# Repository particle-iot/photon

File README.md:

# Photon

The Photon is a tiny WiFi development kit based around USI's WM-N-BM-09 module. This module is a combination of Broadcom's BCM43362 WiFi radio and a STM32F205G microcontroller.

The Photon has a similar footprint and is as close to drop-in compatible as possible with the Spark Core.

### Some highlights of the USI module:

 1. IEEE 802.11b/g/n
 2. Soft AP mode - read smooth WiFi setup process
 3. STM32F205G
 	- 1 MB Flash
 	- 128KB RAM
 	- 120 MHz clock
 4. Measures 12mm x 11mm x 1.3mm

Compared to the Spark Core, the Photon introduces some additional hardware features and changes:

 1. Pin 3V3* is now replaced with VBAT. This pin can be used to power the internal RTC, backup registers and SRAM when the module is put in standby mode.
 2. Pins D1 and D2 can also be used for CAN communication (TX and RX respectively).
 3. Pin A3 now features a DAC (channel 2)
 4. Pin A6 is changed to DAC and exposes a DAC (channel 1).
 5. Pin A7 is changed to WKP (Wakeup). This pin can be used as a standard GPIO, ADC input, PWM or to WAKEUP (rising edge) the module from sleep/standby modes.

A detailed description of the pin mapping can be found in the pin-mapping folder of this repository.
* Sheet 1: Overview of the pin-out.
* Sheet 2: Detailed description of USI module pin-out and its internal mapping to the microcontroller and WiFi radio.

### Pin Descriptions:
- **VIN:** This is the power supply pin to the Photon with a voltage range of 3.6 to 5.5VDC (internally regulated down to 3.3VDC). When the Photon is powered via its USB port, this pin will *ouput* a voltage of approximately 4.7VDC. Why 4.7 and not 5? Well, the actual voltage will be the USB voltage, which is normally 5, minus the forward voltage drop (0.3V) of the protection diode.
- **RST:** This is an active-low reset pin for the Photon.
- **VBAT:** Supply to the internal RTC, backup registers and SRAM (1.8 to 3.3VDC).
- **3V3:** This pin is the output of the on-board regulator and is internally connected to the VDD of the WiFi module. When powering the Photon via VIN or the USB port, this pin will *output* a voltage of 3.3VDC. This pin can also be used to power the Photon directly (max input 3.3VDC). **NOTE:** When powering the Photon via this pin, do not put power on the VIN pin.
- **WKP:** This is an active-high input that allows you to wakeup the module from sleep/deep sleep modes. When not used as a WAKEUP, this pin can also be used as a digital GPIO, ADC input or PWM.
- **D0 - D7:** These are _digital only_ GPIO pins.
- **A0 - A5:** These can be used as digital GPIOs or as ADC inputs.
- **DAC:** This pin can be used as a digital GPIO, ADC input or as a DAC ouput.
- **RX:** Primarily used as UART RX, but can also be used as a digital GPIO, ADC input or PWM.
- **TX:** Primarily used as UART TX, but can also be used as a digital GPIO, ADC input or PWM.

Please review the spreadsheet under the pin-mapping folder to better understand the alternate functions of the GPIO pins.

### Eagle (schematic and pcb layout):
Under the `eagle` folder, you'll find the history of Photon designs.
 1. **cam-drc:** Contains CAM Jobs (for creating gerbers) and DRC (Design Rule) files.
 2. **photon_v001:** The initial photon design.  This version of the design uses the same dimensions as the Spark Core and provides through-hole headers for mounting.
 3. **photon_v010:** Several versions later, numerous tweaks and additions to the schematic, smaller less blinding RGB LED, aligned D7 LED with D7 pin, new SMPS voltage regulator, castellated and non-castellated have been merged, new slightly larger higher gain antenna, Bluetooth Co-existance pins are broken out to pads for a 1.27mm pitch (0.050") connector, pads on the bottom side of the board were added for the RGB LED, and MODE button connections and are centered on the 0.1" grid, and RF switch for software selection of u.FL vs Chip Ant. RF Test board's for versions are included to make tuning of matching components in RF stage easier. There is a second Photon design here with antenna scooted to the left 0.027" to give more clearance between D0 pin and antenna.  C1 in Pi filter was removed to make room for this tighter layout.
 4. **photon_v019:** Several more versions later, numerous tweaks and additions to the schematic, WM-N-BM-09 soldermask updated, added some GND vias, MODE button label changed to SETUP, increased width of top and bottom (short) sides of PCB 20 mils to allow for v-score (overall board height is now 1.44"), SETUP and RESET buttons and RGB led are not centered on the 0.1" grid anymore but they are all still inline with each other, RF switch was changed to a much smaller 1mm version, 0201 dc blocking capacitors added to all RF ports, Pi filter was tuned to match antenna to 50 ohm impedance, half of the pads on the bottom were enlarged to 60 mils square, added fabrication spec.

# License

Designed by Particle. Distributed under a Creative Commons Attribution, Share-Alike license.
Development kits based on this product should be distributed under a similar license.
Commercial products using the Photon as a reference design need not comply with this license; further questions can be sent to hello@particle.io.
Check license.txt for more information.

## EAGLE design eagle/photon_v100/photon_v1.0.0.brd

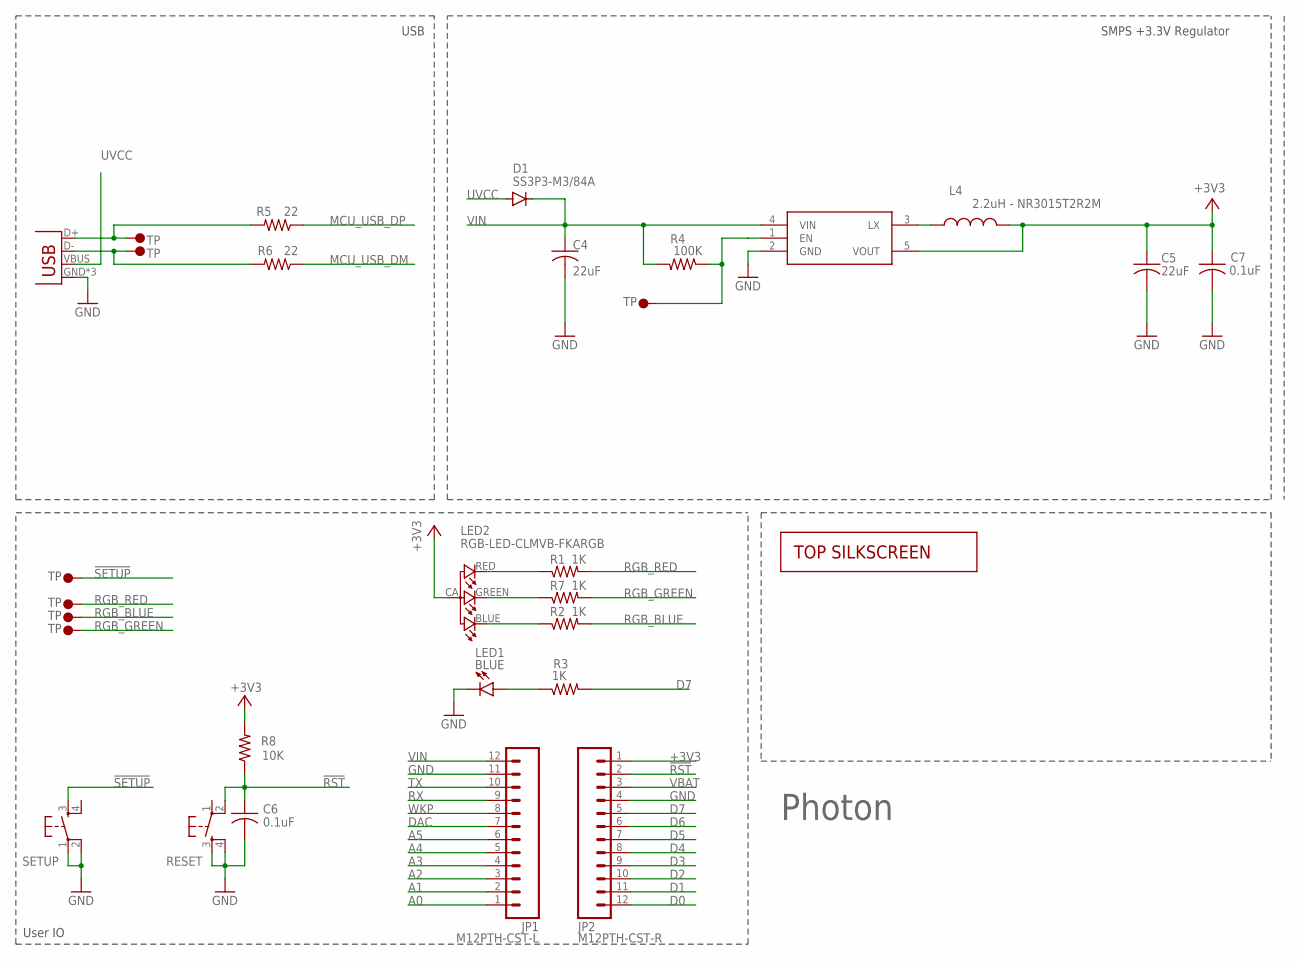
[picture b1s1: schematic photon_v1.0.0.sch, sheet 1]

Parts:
C4, C5: 22uF; C0603_B
C6, C7: 0.1uF; C0402_B
D1: SS3P3-M3/84A; DIODE-DO-220AA(SMP)
JP1: M12PTH-CST-L; 1X12-CASTELLATED
JP2: M12PTH-CST-R; 1X12-CASTELLATED
L4: 2.2uH - NR3015T2R2M; INDUCTOR-NR3015
LED2: RGB-LED-CLMVB-FKARGB; PLCC4-2MM-RGB
LED_USR: BLUE; LED-0603-NO-SS
R1, R2, R3, R7: 1K; R0402_B
R4: 100K; R0402_B
R5, R6: 22; R0402_B
R8: 10K; R0402_B
RESET: KMR211GLFS; TACTILE_SWITCH_SMD
SETUP: KMR211GLFS; TACTILE_SWITCH_SMD
U$1: PHOTON-TOP-SS2; PHOTON-TOP-SS-2
U$3, U$12, U$13, U$14: TP3; TP60_BOT
U$5, U$6, U$7: TP1; TP35_BOT
U$11: R8008-33; SOT23-5
X1: USB-MICROB; USB-MICROB-SLOT-HOLE

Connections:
!RST: C6.1, JP2.2, R8.1, RESET.2; also elsewhere on the board
!SETUP: SETUP.3, U$3.P$1; also elsewhere on the board
+3V3: C5.1, C7.1, JP2.1, L4.2, LED2.CA (1), R8.2, U$11.5 (VOUT); also elsewhere on the board
A0: JP1.1 (12); also elsewhere on the board
A1: JP1.2 (11); also elsewhere on the board
A2: JP1.3 (10); also elsewhere on the board
A3: JP1.4 (9); also elsewhere on the board
A4: JP1.5 (8); also elsewhere on the board
A5: JP1.6 (7); also elsewhere on the board
D0: JP2.12; also elsewhere on the board
D1: JP2.11; also elsewhere on the board
D2: JP2.10; also elsewhere on the board
D3: JP2.9; also elsewhere on the board
D4: JP2.8; also elsewhere on the board
D5: JP2.7; also elsewhere on the board
D6: JP2.6; also elsewhere on the board
D7: JP2.5, R3.2; also elsewhere on the board
DAC: JP1.7 (6); also elsewhere on the board
GND: C4.2, C5.2, C6.2, C7.2, JP1.11 (2), JP2.4, LED_USR.C1 (C), RESET.3, RESET.4, SETUP.1, SETUP.2, U$11.2 (GND), X1.GND, X1.MT1 (GND), X1.MT2 (GND); also elsewhere on the board
LED1: LED_USR.A1 (A), R3.1
MCU_USB_DM: R6.1; also elsewhere on the board
MCU_USB_DP: R5.1; also elsewhere on the board
unnamed: R5.2, U$13.P$1, X1.D+
unnamed: L4.1, U$11.3 (LX)
unnamed: R6.2, U$14.P$1, X1.D-
unnamed: R4.1, U$11.1 (EN), U$12.P$1
unnamed: LED2.BLUE (2), R2.1
unnamed: LED2.GREEN (3), R7.1
unnamed: LED2.RED (4), R1.1
RGB_BLUE: R2.2, U$6.P$1; also elsewhere on the board
RGB_GREEN: R7.2, U$7.P$1; also elsewhere on the board
RGB_RED: R1.2, U$5.P$1; also elsewhere on the board
RX: JP1.9 (4); also elsewhere on the board
TX: JP1.10 (3); also elsewhere on the board
UVCC: D1.ANODE, X1.VBUS
VBAT: JP2.3; also elsewhere on the board
VIN: C4.1, D1.CATHODE, JP1.12 (1), R4.2, U$11.4 (VIN)
WKP: JP1.8 (5); also elsewhere on the board

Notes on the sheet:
SMPS +3.3V Regulator
User IO
USB
Photon

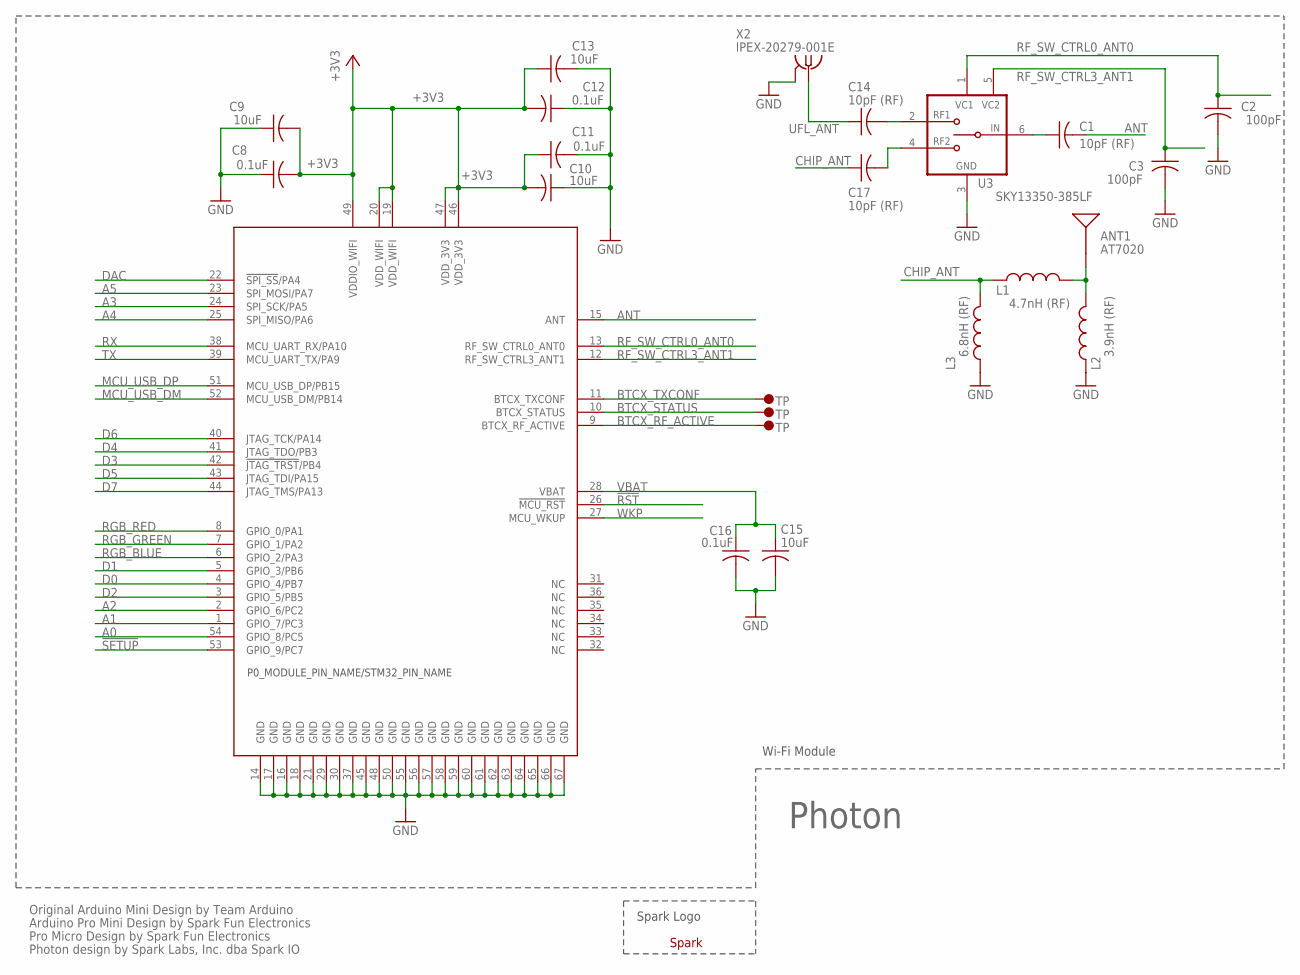
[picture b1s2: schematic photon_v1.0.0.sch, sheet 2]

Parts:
ANT1: AT7020
C1, C14, C17: 10pF (RF); C0201_B
C2, C3: 100pF; C0402_B
C8, C11, C12, C16: 0.1uF; C0402_B
C9, C10, C13, C15: 10uF; C0603_B
L1: 4.7nH (RF); L0402_B
L2: 3.9nH (RF); L0402_B
L3: 6.8nH (RF); L0402_B
U1: WM-N-BM-09
U3: SKY13350-385LF; XFDFN-6
U$2: SPARK_LOGO2
U$8, U$9, U$10: TP1; TP35_BOT
X2: IPEX-20279-001E

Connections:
!RST: U1.26 (!MCU_RST); also elsewhere on the board
!SETUP: U1.53 (GPIO_9/PC7); also elsewhere on the board
+3V3: C8.2, C9.2, C10.2, C11.1, C12.2, C13.1, U1.19 (VDD_WIFI), U1.20 (VDD_WIFI), U1.46 (VDD_3V3), U1.47 (VDD_3V3), U1.49 (VDDIO_WIFI); also elsewhere on the board
A0: U1.54 (GPIO_8/PC5); also elsewhere on the board
A1: U1.1 (GPIO_7/PC3); also elsewhere on the board
A2: U1.2 (GPIO_6/PC2); also elsewhere on the board
A3: U1.24 (SPI_SCK/PA5); also elsewhere on the board
A4: U1.25 (SPI_MISO/PA6); also elsewhere on the board
A5: U1.23 (SPI_MOSI/PA7); also elsewhere on the board
ANT: C1.2, U1.15 (ANT)
BTCX_RF_ACTIVE: U1.9 (BTCX_RF_ACTIVE), U$10.P$1
BTCX_STATUS: U1.10 (BTCX_STATUS), U$9.P$1
BTCX_TXCONF: U1.11 (BTCX_TXCONF), U$8.P$1
CHIP_ANT: C17.1, L1.1, L3.2
D0: U1.4 (GPIO_4/PB7); also elsewhere on the board
D1: U1.5 (GPIO_3/PB6); also elsewhere on the board
D2: U1.3 (GPIO_5/PB5); also elsewhere on the board
D3: U1.42 (!JTAG_TRST!/PB4); also elsewhere on the board
D4: U1.41 (JTAG_TDO/PB3); also elsewhere on the board
D5: U1.43 (JTAG_TDI/PA15); also elsewhere on the board
D6: U1.40 (JTAG_TCK/PA14); also elsewhere on the board
D7: U1.44 (JTAG_TMS/PA13); also elsewhere on the board
DAC: U1.22 (!SPI_SS!/PA4); also elsewhere on the board
GND: C2.2, C3.2, C8.1, C9.1, C10.1, C11.2, C12.1, C13.2, C15.2, C16.2, L2.1, L3.1, U1.14 (GND), U1.16 (GND), U1.17 (GND), U1.18 (GND), U1.21 (GND), U1.29 (GND), U1.30 (GND), U1.37 (GND), U1.45 (GND), U1.48 (GND), U1.50 (GND), U1.55 (GND), U1.56 (GND), U1.57 (GND), U1.58 (GND), U1.59 (GND), U1.60 (GND), U1.61 (GND), U1.62 (GND), U1.63 (GND), U1.64 (GND), U1.65 (GND), U1.66 (GND), U1.67 (GND), U3.3 (GND), X2.2@1 (GND), X2.2@2 (GND); also elsewhere on the board
MCU_USB_DM: U1.52 (MCU_USB_DM/PB14); also elsewhere on the board
MCU_USB_DP: U1.51 (MCU_USB_DP/PB15); also elsewhere on the board
unnamed: ANT1.1, L1.2, L2.2
unnamed: C1.1, U3.6 (IN)
unnamed: C14.2, U3.2 (RF1)
unnamed: C17.2, U3.4 (RF2)
RF_SW_CTRL0_ANT0: C2.1, U1.13 (RF_SW_CTRL0_ANT0), U3.1 (VC1)
RF_SW_CTRL3_ANT1: C3.1, U1.12 (RF_SW_CTRL3_ANT1), U3.5 (VC2)
RGB_BLUE: U1.6 (GPIO_2/PA3); also elsewhere on the board
RGB_GREEN: U1.7 (GPIO_1/PA2); also elsewhere on the board
RGB_RED: U1.8 (GPIO_0/PA1); also elsewhere on the board
RX: U1.38 (MCU_UART_RX/PA10); also elsewhere on the board
TX: U1.39 (MCU_UART_TX/PA9); also elsewhere on the board
UFL_ANT: C14.1, X2.1
VBAT: C15.1, C16.1, U1.28 (VBAT); also elsewhere on the board
WKP: U1.27 (MCU_WKUP); also elsewhere on the board

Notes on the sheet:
Original Arduino Mini Design by Team Arduino
Arduino Pro Mini Design by Spark Fun Electronics
Pro Micro Design by Spark Fun Electronics
Photon design by Spark Labs, Inc. dba Spark IO
Photon
Wi-Fi Module
Spark Logo

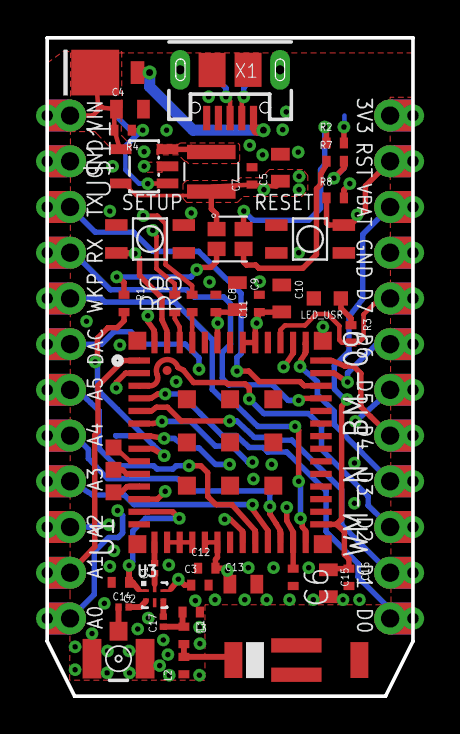
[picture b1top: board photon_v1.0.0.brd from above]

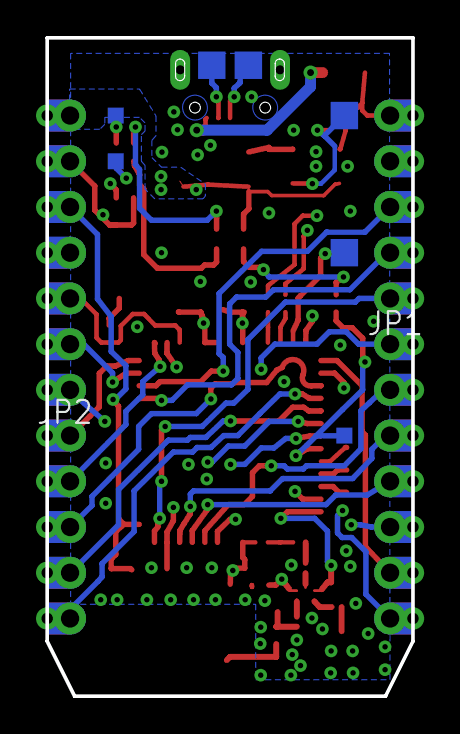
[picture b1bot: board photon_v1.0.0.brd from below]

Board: 4 copper layers, 20.3 x 36.6 mm, 54 parts (5 on the bottom side), 50 nets.

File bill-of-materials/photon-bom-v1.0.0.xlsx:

| Particle | Photon
 | BOM Version | v1.0.0
 | IDENTIFIER | DESCRIPTION | VALUE | VOLTAGE | CURRENT | PWR | TOL | PACKAGE ID | DESIGNATOR | QTY | MFG | MFG P/N
 | ANTENNA | 2.4GHz Ceramic (-1.5dBi) | 2.4GHz |  |  |  |  | 5.0 × 2.0 mm x 2.6mm | ANT1 | 1 | Advanced Ceramic X Johanson | AT7020-E3R0HBA 2450AT43B100E
 | CAPACITOR | Ceramic Capacitor, Low ESR (<50 mOhm), X5R | 22uF | 6.3V |  |  | 10% | 0603 | C4, C5 | 2 | Fenghua | 0603X226K6R3NT
 | CAPACITOR | Ceramic Capacitor, X5R | 0.1uF | 6.3V |  |  | 10% | 0402 | C6, C7, C8, C11, C12, C16 | 6 | Fenghua | 0402B104K100NT
 | CAPACITOR | Ceramic Capacitor, X5R | 100pF | 6.3V |  |  | 10% | 0402 | C2, C3 | 2 | Fenghua | 0402CG101J500NT
 | CAPACITOR | Ceramic Capacitor, X5R | 10uF | 6.3V |  |  | 10% | 0603 | C9, C10, C13, C15 | 4 | Fenghua | 0603X106M6R3NT
 | CAPACITOR (RF) | Ceramic Capacitor, Rated for 2.4GHz, Low ESR (<140 mOhm @ 2.0GHz), X5R | 10pF | 6.3V |  |  | 10% | 0201 | C1, C14, C17 | 3 | Johanson | 250R05L100JV4T
 | CONNECTOR | USB Micro Connector with Slots and Tabs, SMD |  |  |  |  |  | USB Micro-B with Slots | X1 | 1 | Kaweei | CMCUSB-5BFM2G-01-D
 | CONNECTOR | uFL Connector, IPEX-20279-001E, SMD |  |  |  |  |  | SMD | X2 | 1 | Kaweei | P1163-0140R
 | HEADER | Single String, 1.2" Mating Length 0.1" 12-pin |  |  |  |  |  |  | JP1, JP2 | 2 | Kaweei | CP25411-12G-S116-A
 | DIODE | Schottky Rectifier Diode |  | 30V | 3A |  |  | DO-220AA | D1 | 1 | Vishay Semiconductor | SS3P3-M3/84A
 | LED | Blue, SMD | Blue |  |  |  |  | 0603 | LED1 | 1 | Everlight | 19-217/BHC-ZL1M2RY/3T
 | DIODE (LED) | LED RGB, SMD, Common Anode, Diffused | RGB |  |  |  |  | 4-PLCC (3.2 mm x 2.8mm) | LED2 | 1 | Cree | CLMVB-FKA-CFHEHLCBB7A363
 | INDUCTOR | Power Wirewound Inductor, 100KHz, Ferrite, 1212 | 2.2uH |  | 1.5A |  | 20% | 3.0 mm x 3.0 mm | L4 | 1 | Taiyo Yuden | NR3015T2R2M
 | INDUCTOR (RF) | RF Inductor, Rated for 2.4GHz | 3.9nH |  |  |  |  | 0402 | L3 | 1 | Johanson ACX | L-07C3N9SV6T HI1005-1C3N9SMT
 | INDUCTOR (RF) | RF Inductor, Rated for 2.4GHz | 4.7nH |  |  |  |  | 0402 | L1 | 1 | Johanson ACX | L-07C4N7SV6T HI1005-1C4N7SMT
 | INDUCTOR (RF) | RF Inductor, Rated for 2.4GHz | 6.8nH |  |  |  |  | 0402 | L2 | 1 | Johanson ACX | L-07C6N8JV6T HI1005-1C6N8JMT
 | INTEGRATED CIRCUIT | Broadcom Wi-Fi + STM32 MCU |  |  |  |  |  | 11mm x 12mm | U1 | 1 | USI | WM-N-BM-09-S
 | INTEGRATED CIRCUIT | RF Switch SPDT |  |  |  |  |  | UQFN-6 (1x1mm) | U3 | 1 | Skyworks | SKY13350-385LF
 | INTEGRATED CIRCUIT | Switch Mode, High Efficiency PWM Step-Down DC/DC Converter, 1.5MHz | 3.3V |  | 600mA |  |  | SOT-23-5 | U2 | 1 | Richtek | RT8008-33GB
 | PCB | FR4 4-Layer Photon PCB, 1-sided, Matte black soldermask, white silkscreen, 50 o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 |  |  |  |  |  | 2.0 cm x 3.6 cm | PCB | 1 | Consigned | Custom
 | RESISTOR | Chip Resistor | 100k |  |  | 1/10W | 5% | 0402 | R4 | 1 | Fenghua | RC-02W104FT
 | RESISTOR | Chip Resistor | 22R |  |  | 1/10W | 5% | 0402 | R5, R6 | 2 | Fenghua | RC-02W220JT
 | RESISTOR | Chip Resistor | 10k |  |  | 1/10W | 5% | 0402 | R8 | 1 | Fenghua | RC-02W103JT
 | RESISTOR | Chip Resistor | 1k |  |  | 1/10W | 5% | 0402 | R1, R2, R3, R7 | 4 | Fenghua | RC-02W102JT
 | SWITCH | Tactile Switch, Black Button | 160gF |  |  |  |  | 3.6mm x 3.1mm | RESET, SETUP | 2 | Haoyu | TS-1185A-C

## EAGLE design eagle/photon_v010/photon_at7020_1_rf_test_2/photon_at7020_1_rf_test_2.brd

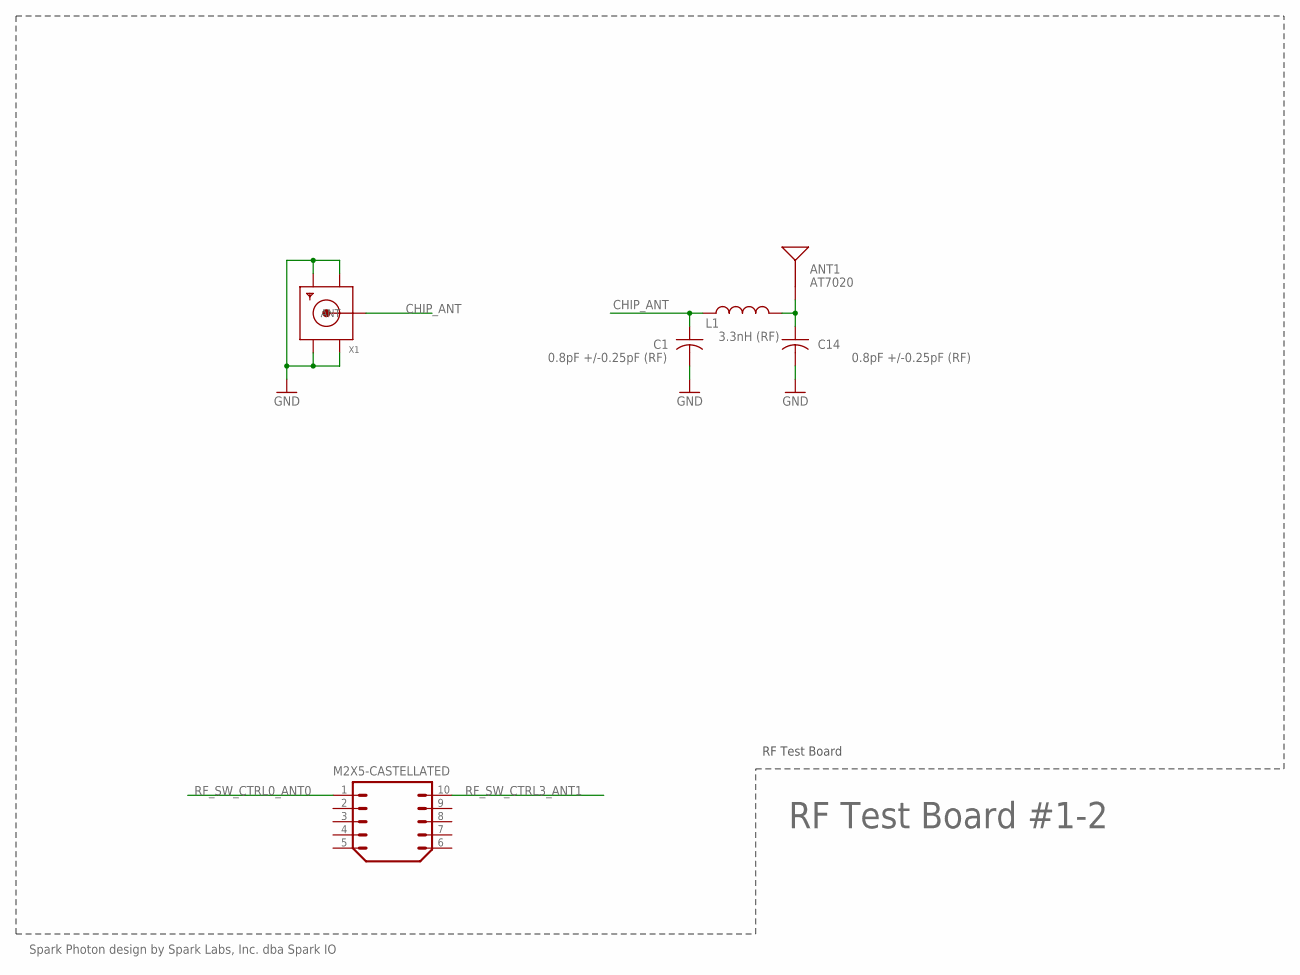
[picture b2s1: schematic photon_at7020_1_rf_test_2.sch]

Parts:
ANT1: AT7020
C1, C14: 0.8pF +/-0.25pF (RF); C0402_B
L1: 3.3nH (RF); L0402_B
M2X5-CASTELLATED: M2X5; 2X5-CASTELLATED
X1: SMACONNECTOR_EDGE; SMA_EDGELAUNCH

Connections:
CHIP_ANT: C1.1, L1.1, X1.P (ANT)
GND: C1.2, C14.2, X1.GND@1 (GND4), X1.GND@2 (GND3), X1.GND@3 (GND2), X1.GND@4 (GND1)
unnamed: ANT1.1, C14.1, L1.2
RF_SW_CTRL0_ANT0: M2X5-CASTELLATED.1
RF_SW_CTRL3_ANT1: M2X5-CASTELLATED.10

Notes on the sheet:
Spark Photon design by Spark Labs, Inc. dba Spark IO
RF Test Board #1-2
RF Test Board

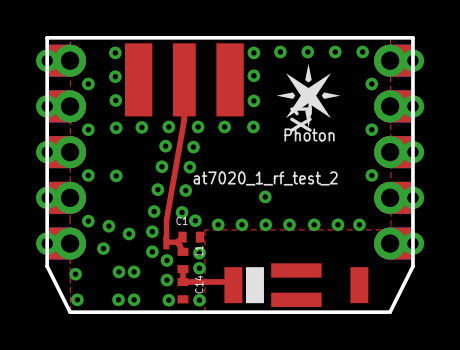
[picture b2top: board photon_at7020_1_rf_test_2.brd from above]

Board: 4 copper layers, 20.3 x 15.2 mm, 6 parts (0 on the bottom side), 3 nets.

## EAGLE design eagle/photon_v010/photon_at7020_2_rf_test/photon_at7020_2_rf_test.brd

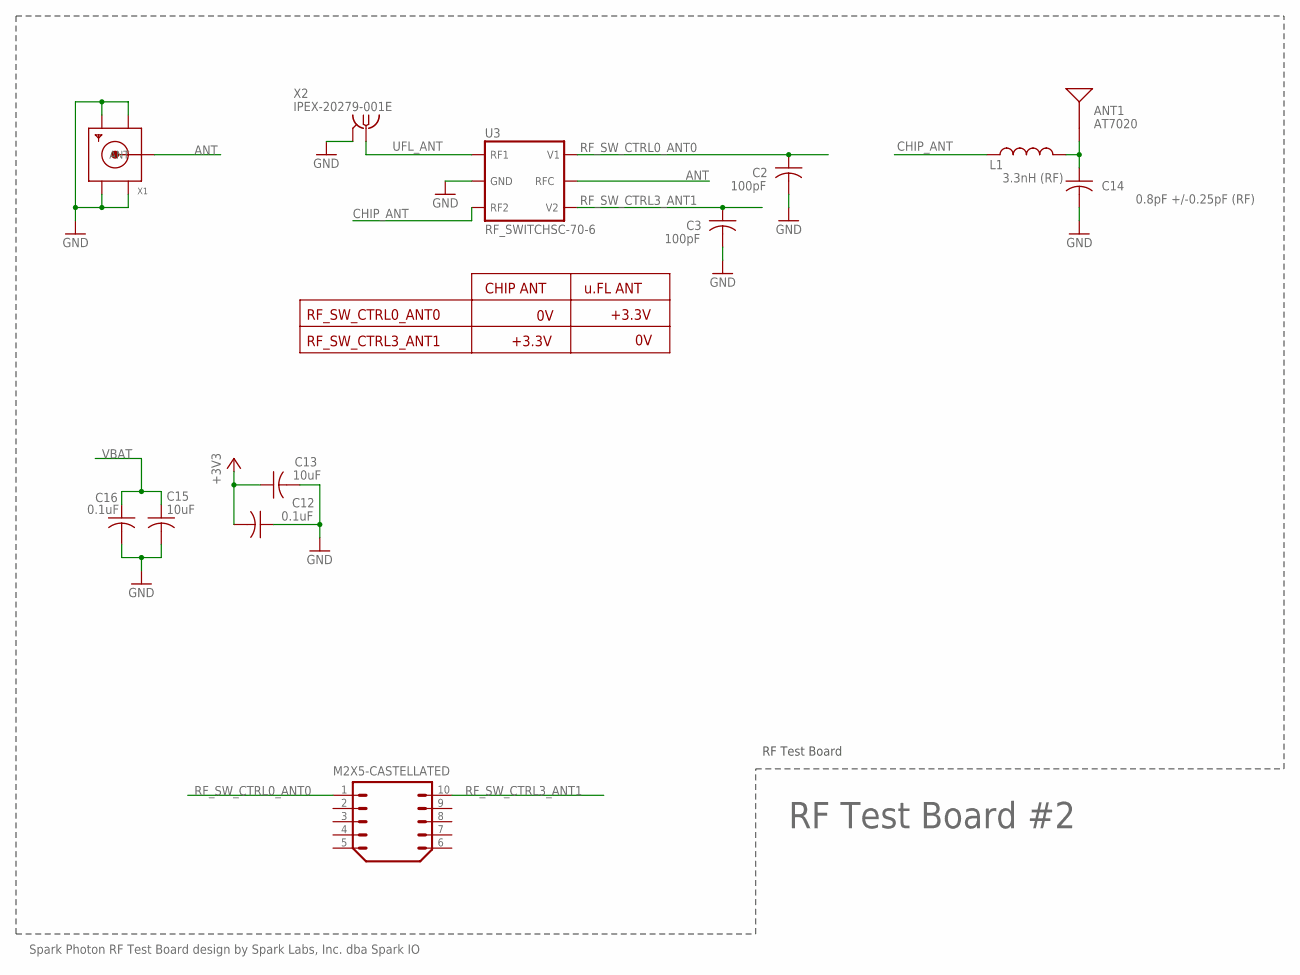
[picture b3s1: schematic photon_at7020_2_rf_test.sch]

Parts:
ANT1: AT7020
C2, C3: 100pF; C0402_B
C12, C16: 0.1uF; C0402_B
C13, C15: 10uF; C0402_B
C14: 0.8pF +/-0.25pF (RF); C0402_B
L1: 3.3nH (RF); L0402_B
M2X5-CASTELLATED: M2X5; 2X5-CASTELLATED
U3: RF_SWITCHSC-70-6; SC70-6
X1: SMACONNECTOR_EDGE; SMA_EDGELAUNCH
X2: IPEX-20279-001E

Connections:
+3V3: C12.2, C13.1
ANT: U3.5 (RFC), X1.P (ANT)
CHIP_ANT: L1.1, U3.3 (RF2)
GND: C2.2, C3.2, C12.1, C13.2, C14.2, C15.2, C16.2, U3.2 (GND), X1.GND@1 (GND4), X1.GND@2 (GND3), X1.GND@3 (GND2), X1.GND@4 (GND1), X2.2@1 (GND), X2.2@2 (GND)
unnamed: ANT1.1, C14.1, L1.2
RF_SW_CTRL0_ANT0: C2.1, M2X5-CASTELLATED.1, U3.6 (V1)
RF_SW_CTRL3_ANT1: C3.1, M2X5-CASTELLATED.10, U3.4 (V2)
UFL_ANT: U3.1 (RF1), X2.1
VBAT: C15.1, C16.1

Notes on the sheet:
Spark Photon RF Test Board design by Spark Labs, Inc. dba Spark IO
RF Test Board #2
RF Test Board
RF_SW_CTRL0_ANT0
RF_SW_CTRL3_ANT1
+3.3V
CHIP ANT
u.FL ANT

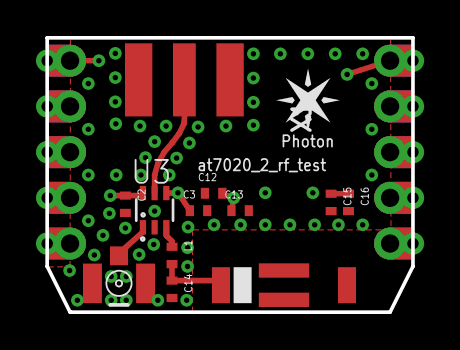
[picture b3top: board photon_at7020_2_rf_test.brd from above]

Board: 4 copper layers, 20.3 x 15.2 mm, 13 parts (0 on the bottom side), 9 nets.

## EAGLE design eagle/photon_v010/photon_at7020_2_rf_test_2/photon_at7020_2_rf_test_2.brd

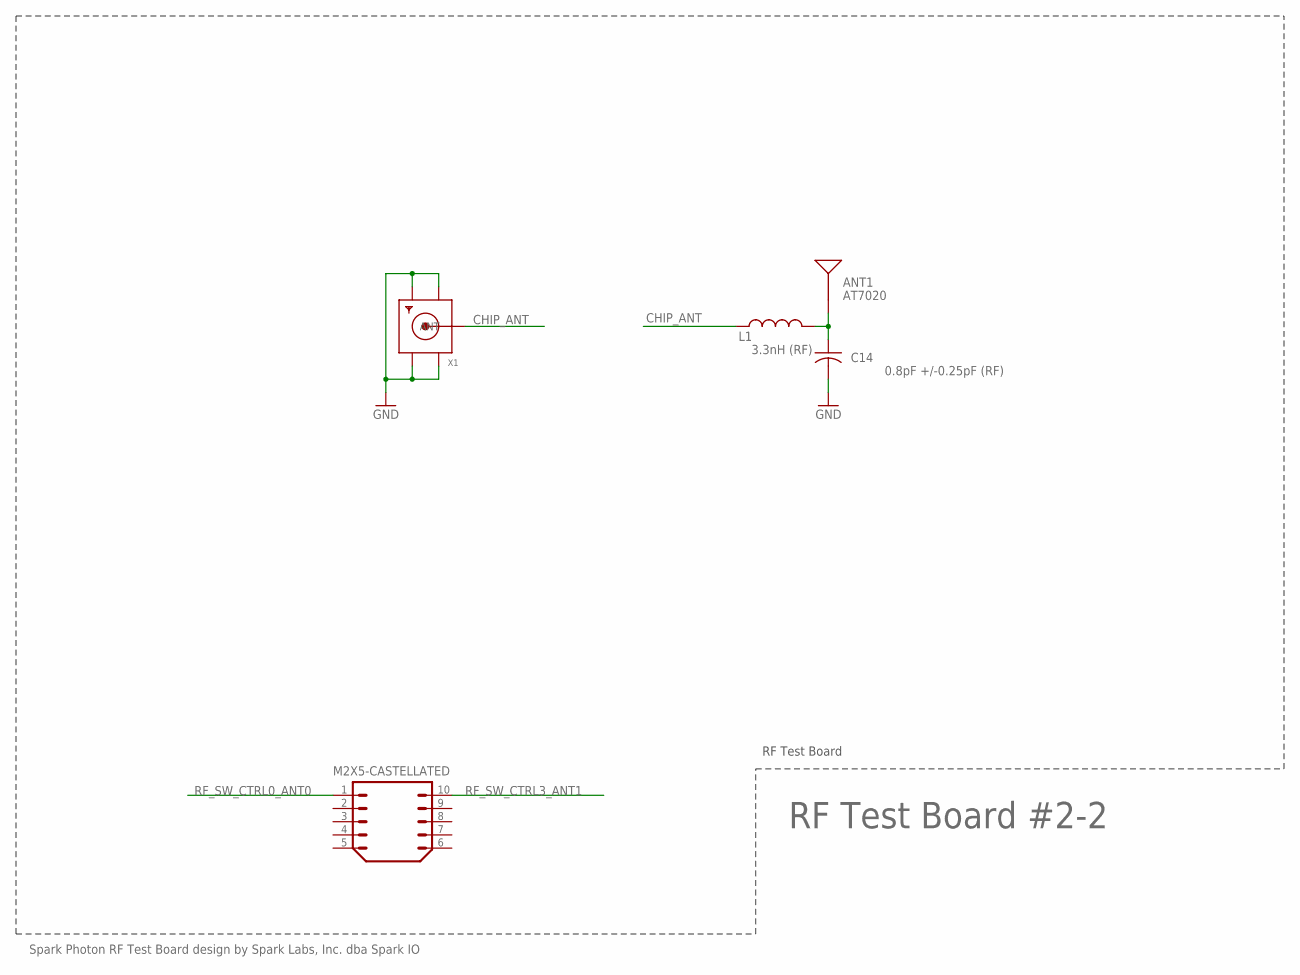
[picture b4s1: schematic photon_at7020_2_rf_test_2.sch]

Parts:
ANT1: AT7020
C14: 0.8pF +/-0.25pF (RF); C0402_B
L1: 3.3nH (RF); L0402_B
M2X5-CASTELLATED: M2X5; 2X5-CASTELLATED
X1: SMACONNECTOR_EDGE; SMA_EDGELAUNCH

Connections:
CHIP_ANT: L1.1, X1.P (ANT)
GND: C14.2, X1.GND@1 (GND4), X1.GND@2 (GND3), X1.GND@3 (GND2), X1.GND@4 (GND1)
unnamed: ANT1.1, C14.1, L1.2
RF_SW_CTRL0_ANT0: M2X5-CASTELLATED.1
RF_SW_CTRL3_ANT1: M2X5-CASTELLATED.10

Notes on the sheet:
Spark Photon RF Test Board design by Spark Labs, Inc. dba Spark IO
RF Test Board #2-2
RF Test Board

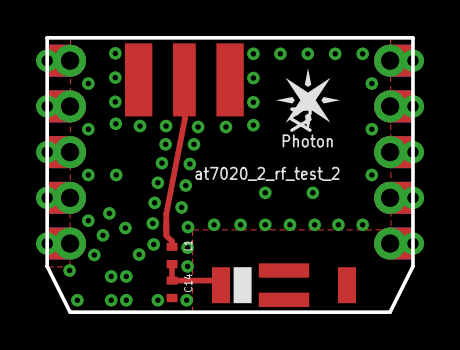
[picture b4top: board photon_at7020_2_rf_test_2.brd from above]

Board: 4 copper layers, 20.3 x 15.2 mm, 5 parts (0 on the bottom side), 3 nets.

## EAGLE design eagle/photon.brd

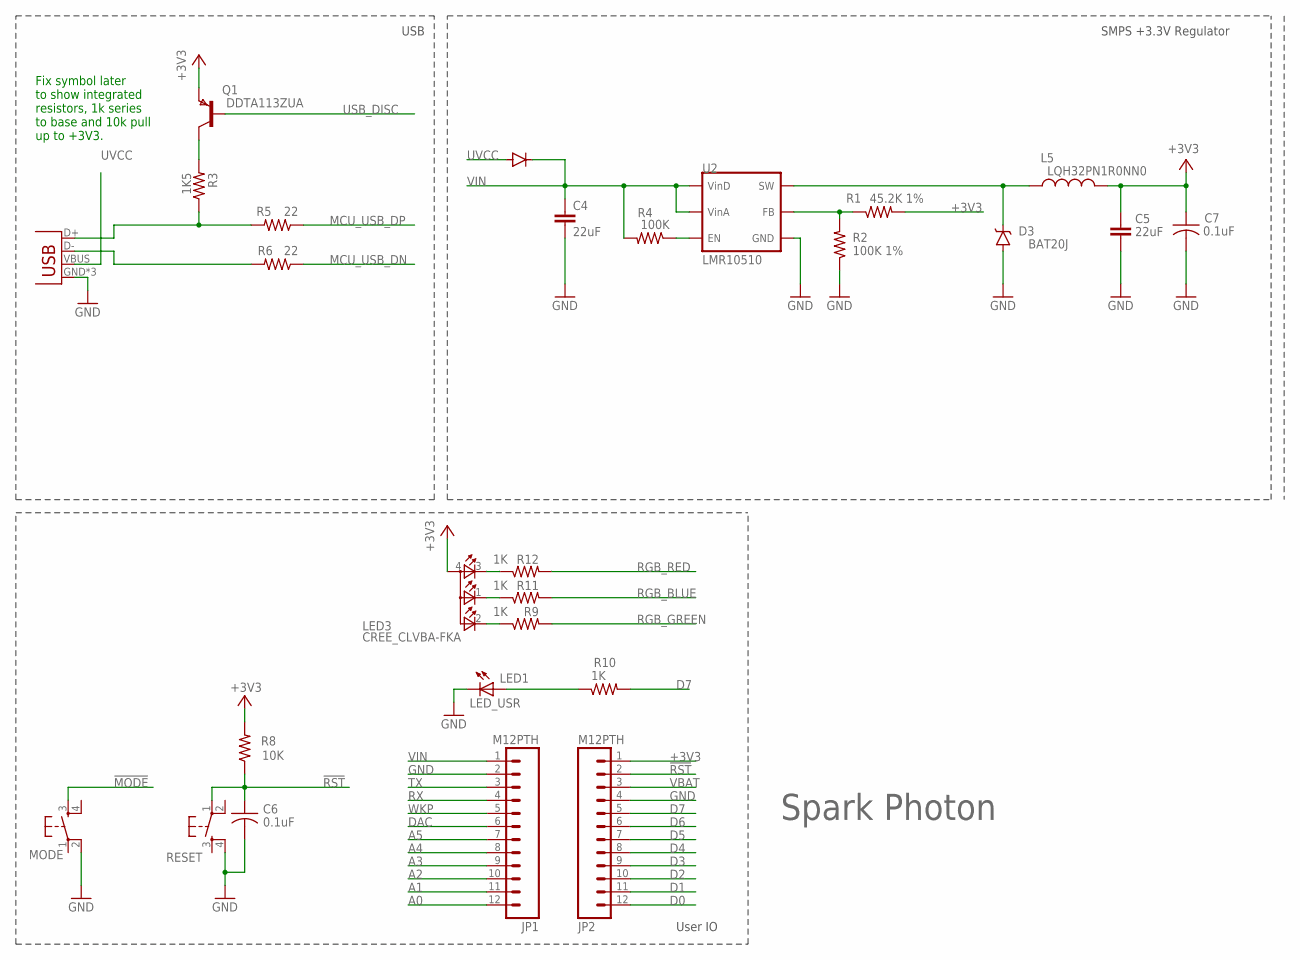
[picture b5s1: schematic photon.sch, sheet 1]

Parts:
C4, C5: 22uF; C0603
C6, C7: 0.1uF; C0402
D1: DIODE; DIODE-DO-220AA(SMP)
D3: BAT20J; SOD-323
JP1, JP2: M12PTH; 1X12-SMALL-PADS
L5: LQH32PN1R0NN0; 1210
LED3: CREE_CLVBA-FKA; P-LCC-4-3
LED_USR: LED0603; LED-0603
MODE: KMR211GLFS; TACTILE_SWITCH_SMD
Q1: DDTA113ZUA; SOT323
R1: 45.2K 1%; R0402
R2: 100K 1%; R0402
R3: 1K5; R0402
R4: 100K; R0402
R5, R6: 22; R0402
R8: 10K; R0402
R9, R10, R11, R12: 1K; R0402
RESET: KMR211GLFS; TACTILE_SWITCH_SMD
U2: LMR10510; WSON-6-PAD
X1: USB-MICROB; USB-MICROB-SLOT-HOLE

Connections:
!MODE: MODE.3; also elsewhere on the board
!RST: C6.1, JP2.2, R8.1, RESET.1; also elsewhere on the board
+3V3: C5.1, C7.1, JP2.1, L5.2, LED3.4 (A2), Q1.3 (E), R1.2, R8.2
A0: JP1.12; also elsewhere on the board
A1: JP1.11; also elsewhere on the board
A2: JP1.10; also elsewhere on the board
A3: JP1.9; also elsewhere on the board
A4: JP1.8; also elsewhere on the board
A5: JP1.7; also elsewhere on the board
D0: JP2.12; also elsewhere on the board
D1: JP2.11; also elsewhere on the board
D2: JP2.10; also elsewhere on the board
D3: JP2.9; also elsewhere on the board
D4: JP2.8; also elsewhere on the board
D5: JP2.7; also elsewhere on the board
D6: JP2.6; also elsewhere on the board
D7: JP2.5, R10.2
DAC: JP1.6; also elsewhere on the board
EN: R4.1, U2.6 (EN)
FB: R1.1, R2.2, U2.1 (FB)
GND: C4.2, C5.2, C6.2, C7.2, D3.A, JP1.2, JP2.4, LED_USR.C, MODE.2, R2.1, RESET.4, U2.2 (GND), U2.PAD (GND), X1.GND, X1.MT1 (GND), X1.MT2 (GND); also elsewhere on the board
LED1: LED_USR.A, R10.1
MCU_USB_DN: R6.1; also elsewhere on the board
MCU_USB_DP: R5.1; also elsewhere on the board
unnamed: R3.1, R5.2, X1.D+
unnamed: R6.2, X1.D-
unnamed: Q1.1 (C), R3.2
unnamed: LED3.1 (CBLUE), R11.1
unnamed: LED3.2 (CGREEN), R9.1
unnamed: LED3.3 (CRED), R12.1
RGB_BLUE: R11.2; also elsewhere on the board
RGB_GREEN: R9.2; also elsewhere on the board
RGB_RED: R12.2; also elsewhere on the board
RX: JP1.4; also elsewhere on the board
SW: D3.C, L5.1, U2.3 (SW)
TX: JP1.3; also elsewhere on the board
USB_DISC: Q1.2 (B); also elsewhere on the board
UVCC: D1.ANODE, X1.VBUS
VBAT: JP2.3; also elsewhere on the board
VIN: C4.1, D1.CATHODE, JP1.1, R4.2, U2.4 (VIND), U2.5 (VINA)
WKP: JP1.5; also elsewhere on the board

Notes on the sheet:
SMPS +3.3V Regulator
User IO
USB
Spark Photon
Fix symbol later to show integrated resistors, 1k series to base and 10k pull up to +3V3.

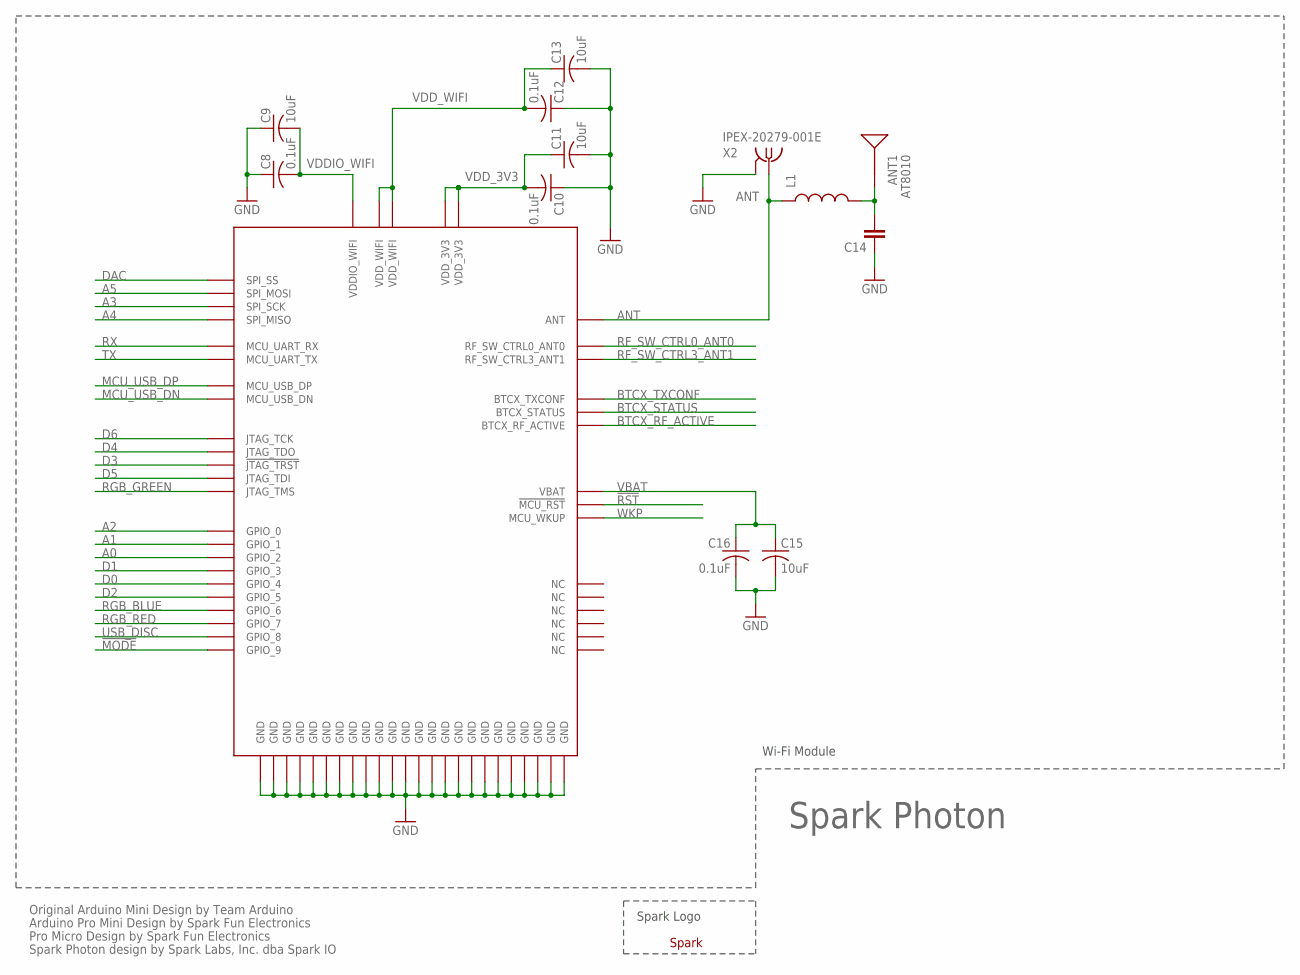
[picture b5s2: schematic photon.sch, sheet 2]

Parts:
ANT1: AT8010
C8, C10, C12, C16: 0.1uF; C0402
C9, C11, C13, C15: 10uF; C0402
C14: CAP0603-CAP; 0603-CAP
L1: INDUCTOR-SPARKFUN0603; 0603
U1: WM-N-BM-09
U$2: SPARK_LOGO2
X2: IPEX-20279-001E

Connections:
!MODE: U1.P$53 (GPIO_9); also elsewhere on the board
!RST: U1.P$26 (!MCU_RST); also elsewhere on the board
A0: U1.P$6 (GPIO_2); also elsewhere on the board
A1: U1.P$7 (GPIO_1); also elsewhere on the board
A2: U1.P$8 (GPIO_0); also elsewhere on the board
A3: U1.P$24 (SPI_SCK); also elsewhere on the board
A4: U1.P$25 (SPI_MISO); also elsewhere on the board
A5: U1.P$23 (SPI_MOSI); also elsewhere on the board
ANT: L1.1, U1.P$15 (ANT), X2.1
BTCX_RF_ACTIVE: U1.P$9 (BTCX_RF_ACTIVE)
BTCX_STATUS: U1.P$10 (BTCX_STATUS)
BTCX_TXCONF: U1.P$11 (BTCX_TXCONF)
D0: U1.P$4 (GPIO_4); also elsewhere on the board
D1: U1.P$5 (GPIO_3); also elsewhere on the board
D2: U1.P$3 (GPIO_5); also elsewhere on the board
D3: U1.P$42 (!JTAG_TRST); also elsewhere on the board
D4: U1.P$41 (JTAG_TDO); also elsewhere on the board
D5: U1.P$43 (JTAG_TDI); also elsewhere on the board
D6: U1.P$40 (JTAG_TCK); also elsewhere on the board
DAC: U1.P$22 (SPI_SS); also elsewhere on the board
GND: C8.1, C9.1, C10.1, C11.2, C12.1, C13.2, C14.1, C15.2, C16.2, U1.P$14 (GND), U1.P$16 (GND), U1.P$17 (GND), U1.P$18 (GND), U1.P$21 (GND), U1.P$29 (GND), U1.P$30 (GND), U1.P$37 (GND), U1.P$45 (GND), U1.P$48 (GND), U1.P$50 (GND), U1.P$55 (GND), U1.P$56 (GND), U1.P$57 (GND), U1.P$58 (GND), U1.P$59 (GND), U1.P$60 (GND), U1.P$61 (GND), U1.P$62 (GND), U1.P$63 (GND), U1.P$64 (GND), U1.P$65 (GND), U1.P$66 (GND), U1.P$67 (GND), X2.2@1 (GND), X2.2@2 (GND); also elsewhere on the board
MCU_USB_DN: U1.P$52 (MCU_USB_DN); also elsewhere on the board
MCU_USB_DP: U1.P$51 (MCU_USB_DP); also elsewhere on the board
unnamed: ANT1.SIG, C14.2, L1.2
RF_SW_CTRL0_ANT0: U1.P$13 (RF_SW_CTRL0_ANT0)
RF_SW_CTRL3_ANT1: U1.P$12 (RF_SW_CTRL3_ANT1)
RGB_BLUE: U1.P$2 (GPIO_6); also elsewhere on the board
RGB_GREEN: U1.P$44 (JTAG_TMS); also elsewhere on the board
RGB_RED: U1.P$1 (GPIO_7); also elsewhere on the board
RX: U1.P$38 (MCU_UART_RX); also elsewhere on the board
TX: U1.P$39 (MCU_UART_TX); also elsewhere on the board
USB_DISC: U1.P$54 (GPIO_8); also elsewhere on the board
VBAT: C15.1, C16.1, U1.P$28 (VBAT); also elsewhere on the board
VDDIO_WIFI: C8.2, C9.2, U1.P$49 (VDDIO_WIFI)
VDD_3V3: C10.2, C11.1, U1.P$46 (VDD_3V3), U1.P$47 (VDD_3V3)
VDD_WIFI: C12.2, C13.1, U1.P$19 (VDD_WIFI), U1.P$20 (VDD_WIFI)
WKP: U1.P$27 (MCU_WKUP); also elsewhere on the board

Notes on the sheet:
Original Arduino Mini Design by Team Arduino
Arduino Pro Mini Design by Spark Fun Electronics
Pro Micro Design by Spark Fun Electronics
Spark Photon design by Spark Labs, Inc. dba Spark IO
Spark Photon
Wi-Fi Module
Spark Logo

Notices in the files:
parts and their libraries:
SparkFun-Capacitors: Licensing: Creative Commons ShareAlike 4.0 International - https://creativecommons.org/licenses/by-sa/4.0
